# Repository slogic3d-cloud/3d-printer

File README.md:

# Amethyst-Board
## About
Just a board with an external antenna and an ESP32 chip, a USB-C connector and 38 pins.
It supports 3.3V and 5V, and many GND pins.

## Why I built this
I built it because of fun and I need a dev-board which I understood. It helped me to learn more about creating schematics and pcbs.

## Pictures
Under this text is the pictures for the schematics, it is not the best work but it still functions.

Below this short sentence you can see a picture from the PCB, actually it is a good beginner work.

## Pinout
### Header J2 (left)

| Pin | Signal | Notes |
|:---:|:---|:---|
| 1 | **3V3** | 3.3 V power |
| 2 | **EN** | Reset (active low) |
| 3 | IO36 (VP) | Input only |
| 4 | IO39 (VN) | Input only |
| 5 | IO34 | Input only |
| 6 | IO35 | Input only |
| 7 | IO32 | |
| 8 | IO33 | |
| 9 | IO25 | DAC1 |
| 10 | IO26 | DAC2 |
| 11 | IO27 | |
| 12 | IO14 | |
| 13 | IO12 | ⚠️ Strapping – must be LOW at boot |
| 14 | **GND** | |
| 15 | IO13 | |
| 16 | **GND** | |
| 17 | **3V3** | 3.3 V power |
| 18 | **5V** | USB 5 V (after fuse) |
| 19 | **5V** | USB 5 V (after fuse) |

### Header J3 (right)

| Pin | Signal | Notes |
|:---:|:---|:---|
| 1 | **GND** | |
| 2 | IO23 | |
| 3 | IO22 | I²C SCL (default) |
| 4 | TX0 (IO1) | USB serial |
| 5 | RX0 (IO3) | USB serial |
| 6 | IO21 | I²C SDA (default) |
| 7 | **GND** | |
| 8 | IO19 | |
| 9 | IO18 | |
| 10 | IO5 | ⚠️ Strapping |
| 11 | IO17 | |
| 12 | IO16 | |
| 13 | IO4 | |
| 14 | IO0 | ⚠️ Strapping – BOOT button |
| 15 | IO2 | ⚠️ Strapping |
| 16 | IO15 | ⚠️ Strapping |
| 17 | **GND** | |
| 18 | **3V3** | 3.3 V power |
| 19 | **5V** | USB 5 V (after fuse) |

## BOM
See [BOM.csv](BOM.csv)

Cost: €84.49 (≈ $97)

## What did the ai
I used ai for correcting and helping me out so that i didn't make that much mistakes.
As ai i used "Claude Code". With him we brainstormed the Project idea. 
He made the schematic review and error finding, the Pin-to-Pint connection list, the Component and footprint suggestions, the Pinout table formatting.
He helped me also with the writing, spelling and grammar in the different texts.
The Repository organization (folder, .gitignore, license file) was made by him like the BOM.csv structure. 
Important to say is that he helped at the PCB review and how KiCad works.

### What i did myself:
Schematics drawing
Components placement
PCB routing
DRC fixes
Gerber and Step export
README and journal writing

## License
License: CC BY-NC-SA 4.0
Meaning: do not sell it, further develop and private use are allowed

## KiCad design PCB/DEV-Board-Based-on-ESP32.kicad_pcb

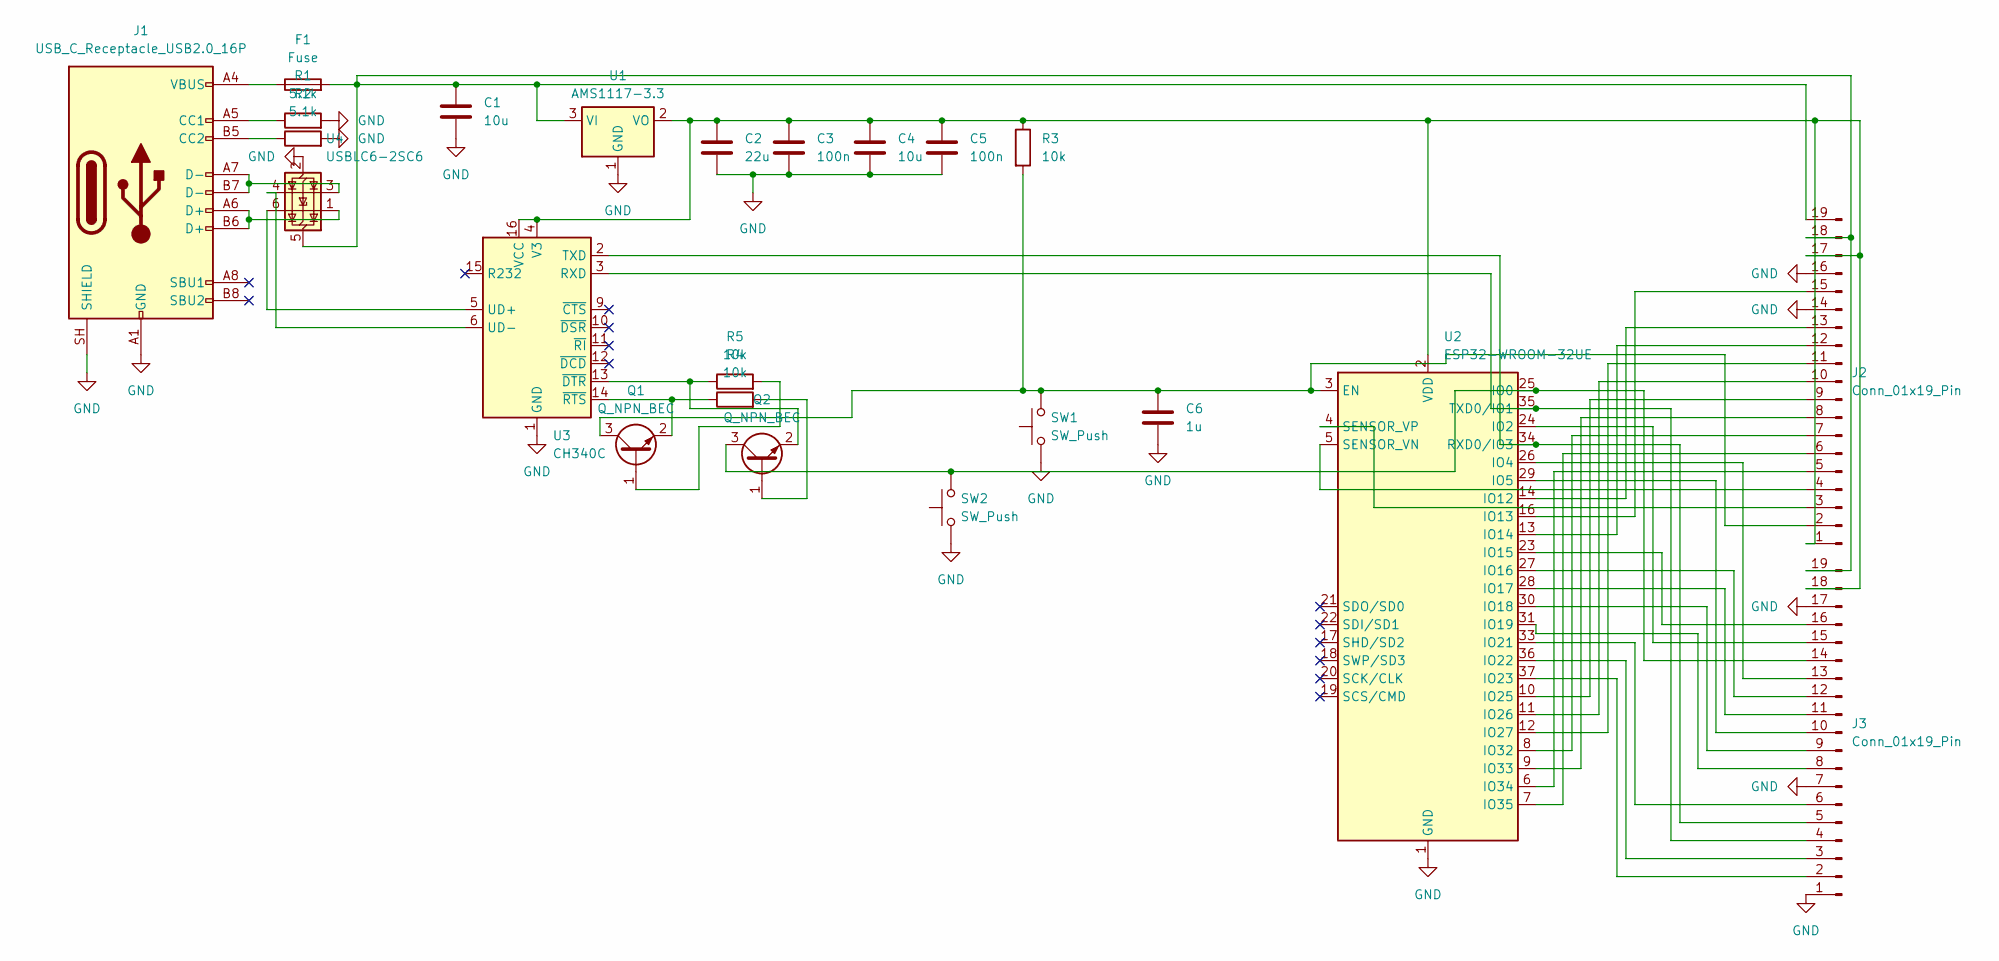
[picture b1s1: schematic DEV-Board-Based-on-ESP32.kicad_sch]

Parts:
C1, C4: 10u; C_0805_2012Metric
C2: 22u; C_0805_2012Metric
C3, C5: 100n; C_0805_2012Metric
C6: 1u; C_0805_2012Metric
F1: Fuse; Fuse_1206_3216Metric
J1: USB_C_Receptacle_USB2.0_16P; USB_C_Receptacle_HRO_TYPE-C-31-M-12
J2, J3: Conn_01x19_Pin; PinHeader_1x19_P2.54mm_Vertical
Q1, Q2: Q_NPN_BEC; SOT-23
R1, R2: 5.1k; R_0603_1608Metric
R3, R4, R5: 10k; R_0603_1608Metric
SW1, SW2: SW_Push; SW_SPST_PTS645Sx43SMTR92
U1: AMS1117-3.3; SOT-223-3_TabPin2
U2: ESP32-WROOM-32UE; ESP32-WROOM-32U
U3: CH340C; SOIC-16_3.9x9.9mm_P1.27mm
U4: USBLC6-2SC6; SOT-23-6

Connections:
GND: C1.2, C2.2, C3.2, C4.2, C5.2, C6.2, J1.A1 (GND), J1.A12 (GND), J1.B1 (GND), J1.B12 (GND), J1.SH (SHIELD), J2.14, J2.16, J3.1, J3.7, J3.17, R1.2, R2.2, SW1.1, SW2.1, U1.1 (GND), U2.1 (GND), U2.15 (GND), U2.38 (GND), U2.39 (GND), U3.1 (GND), U4.2 (GND)
unnamed: F1.1, J1.A4 (VBUS), J1.A9 (VBUS), J1.B4 (VBUS), J1.B9 (VBUS)
unnamed: J1.A5 (CC1), R1.1
unnamed: J1.B5 (CC2), R2.1
unnamed: J1.A6 (D+), J1.B6 (D+), U4.1 (I/O1)
unnamed: J1.A7 (D-), J1.B7 (D-), U4.3 (I/O2)
unnamed: C2.1, C3.1, C4.1, C5.1, J2.1, J2.17, J3.18, R3.1, U1.2 (VO), U2.2 (VDD), U3.4 (V3), U3.16 (VCC)
unnamed: C6.1, J2.2, Q1.3 (C), R3.2, SW1.2, U2.3 (EN)
unnamed: J2.3, U2.4 (SENSOR_VP)
unnamed: J2.4, U2.5 (SENSOR_VN)
unnamed: J2.5, U2.6 (IO34)
unnamed: J2.6, U2.7 (IO35)
unnamed: J2.7, U2.8 (IO32)
unnamed: J2.8, U2.9 (IO33)
unnamed: J2.9, U2.10 (IO25)
unnamed: J2.10, U2.11 (IO26)
unnamed: J2.11, U2.12 (IO27)
unnamed: J2.12, U2.13 (IO14)
unnamed: J2.13, U2.14 (IO12)
unnamed: J2.15, U2.16 (IO13)
unnamed: C1.1, F1.2, J2.18, J2.19, J3.19, U1.3 (VI), U4.5 (VBUS)
unnamed: J3.2, U2.37 (IO23)
unnamed: J3.3, U2.36 (IO22)
unnamed: J3.4, U2.35 (TXD0/IO1), U3.3 (RXD)
unnamed: J3.5, U2.34 (RXD0/IO3), U3.2 (TXD)
unnamed: J3.6, U2.33 (IO21)
unnamed: J3.8, U2.31 (IO19)
unnamed: J3.9, U2.30 (IO18)
unnamed: J3.10, U2.29 (IO5)
unnamed: J3.11, U2.28 (IO17)
unnamed: J3.12, U2.27 (IO16)
unnamed: J3.13, U2.26 (IO4)
unnamed: J3.14, Q2.3 (C), SW2.2, U2.25 (IO0)
unnamed: J3.15, U2.24 (IO2)
unnamed: J3.16, U2.23 (IO15)
unnamed: Q1.1 (B), R5.2
unnamed: Q1.2 (E), R4.1, U3.14 (~RTS)
unnamed: Q2.1 (B), R4.2
unnamed: Q2.2 (E), R5.1, U3.13 (~DTR)
unnamed: U3.5 (UD+), U4.6 (I/O1)
unnamed: U3.6 (UD-), U4.4 (I/O2)

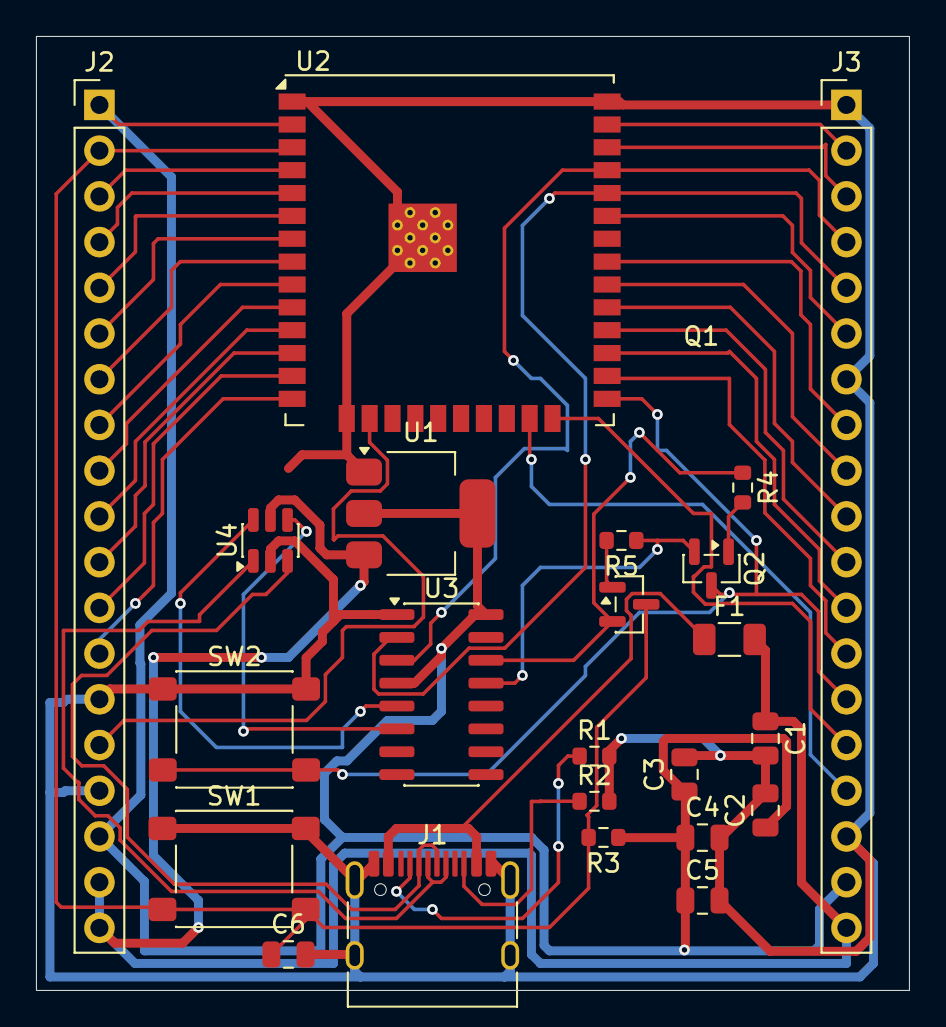
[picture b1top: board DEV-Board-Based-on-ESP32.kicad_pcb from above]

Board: 2 copper layers, 48.5 x 53.0 mm, 23 parts (0 on the bottom side), 41 nets.

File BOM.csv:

Reference,Value,Footprint,Quantity,Unit Price (USD),Total (USD),Link,Notes
U1,AMS1117-3.3,SOT-223-3_TabPin2,1,,,,
U2,ESP32-WROOM-32UE,ESP32-WROOM-32U,1,,,,
U3,CH340C,SOIC-16_3.9x9.9mm_P1.27mm,1,,,,
U4,USBLC6-2SC6,SOT-23-6,1,,,,
F1,Polyfuse 500mA,Fuse_1206_3216Metric,1,,,,
J1,USB-C 16P (HRO TYPE-C-31-M-12),USB_C_Receptacle_HRO_TYPE-C-31-M-12,1,,,,
"J2, J3",Pin header 1x19 2.54mm,PinHeader_1x19_P2.54mm_Vertical,2,,,,
"SW1, SW2",Push button,SW_SPST_PTS645Sx43SMTR92,2,,,,
"Q1, Q2",NPN (MMBT3904/S8050),SOT-23,2,,,,
"R1, R2",5.1k,R_0603_1608Metric,2,,,,
"R3, R4, R5",10k,R_0603_1608Metric,3,,,,
"C1, C4",10u,C_0805_2012Metric,2,,,,
C2,22u,C_0805_2012Metric,1,,,,
"C3, C5",100n,C_0805_2012Metric,2,,,,
C6,1u,C_0805_2012Metric,1,,,,
ANT1,2.4 GHz antenna U.FL/IPEX MHF1,-,1,,,,not on PCB
PCB,JLCPCB 2-layer + assembly,-,1,,,,
Shipping,JLCPCB,-,1,,,,
